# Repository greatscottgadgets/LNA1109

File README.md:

# LNA1109

LNA1109 is an in-line SMA Low Noise Amplifier with SAW filter.

## hardware notes

Schematic and layout files were designed in KiCad, an open source electronic
design automation package.

This design may be assembled with any SAW filter with a standard 1.1 x 0.9 mm
footprint.

The PCB is designed to fit the Crystek SMA-KIT-1.5MF housing.

```
order of copper layers:
    Copper 1:  F (front)
    Copper 2:  In1
    Copper 3:  In2
    Copper 4:  B (back)

PCB description: 4 layer PCB 0.8 mm
    Copper       1:  0.035 mm (1 oz)
    Dielectric 1-2:  0.2 mm prepreg
    Copper       2:  0.0175 mm (0.5 oz)
    Dielectric 2-3:  0.265 mm core
    Copper       3:  0.0175 mm (0.5 oz)
    Dielectric 3-4:  0.2 mm prepreg
    Copper       4:  0.035 mm (1 oz)

7628 prepreg with Er=4.6
double side solder mask green
double side silkscreen white
7 mil minimum trace width
5 mil minimum isolation
```

PCBs of this specification are available from JLCPCB (JLC7628 4-layer 0.8 mm stackup).

## frequency options

LNA1109 may be populated with different components to support various frequency
bands.

frequency band | U4 part number       | L1-L4 part number | C1-C6 part number
---------------|----------------------|-------------------|-------------------
902-928 MHz    | FAR-F5QA-915M00-M2AK | HK1005R10J-T      | GCM1555C1H470JA16D
1559-1606 MHz  | F6QA1G582H2JM        | HK100539NJ-T      | GCM1555C1H180JA16D
2402-2483 MHz  | F6FC2G441H4PE        | HK100527NJ-T      | GCM1555C1H100JA16D

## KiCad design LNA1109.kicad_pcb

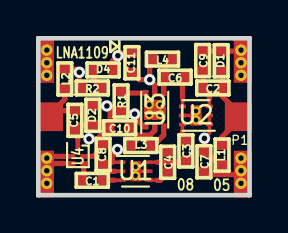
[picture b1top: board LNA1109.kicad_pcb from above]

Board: 4 copper layers, 11.7 x 8.7 mm, 25 parts (0 on the bottom side), 17 nets.

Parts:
C1, C2, C3, C4, C5, C6: 47pF; 0402
C7, C8: 100pF; 0402
C9: 1pF; 0402
C10, C11: 1uF; 0402
D1, D2: D_TVS; 0402
D4: LNALED; 0402
L1, L2, L3, L4: 100nH; 0402
P1: SMA-KIT-1.5MF
R1: 3k; 0402
R2: 470; 0402
U1, U2: SWITCH; GRF6011
U3: LNA; TSLP-7-1
U4: SAW; F5Q

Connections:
GND: C7.1, C8.1, C9.2, C10.1, C11.1, D1.1, D2.1, D4.1, P1.2, P1.4, U1.5, U1.7, U2.5, U2.7, U3.7, U4.2, U4.3, U4.5
unnamed: C1.1, U4.4
unnamed: C1.2, U1.3
unnamed: C2.1, C9.1, U2.3
unnamed: C2.2, D1.2, L1.1, P1.1
unnamed: C3.1, U1.6
unnamed: C3.2, U2.6
unnamed: C4.1, U1.4
unnamed: C4.2, L3.1, U3.3
unnamed: C5.1, L2.1, P1.3
unnamed: C5.2, D2.2, U4.1
unnamed: C6.1, L4.2, U3.4
unnamed: C6.2, U2.4
unnamed: C10.2, L3.2, U3.2
unnamed: D4.2, R2.2
unnamed: R1.2, U3.6
VCC: C7.2, C8.2, C11.2, L1.2, L2.2, L4.1, R1.1, R2.1, U1.1, U1.2, U2.1, U2.2, U3.1, U3.5

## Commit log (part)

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2020-08-05 initial commit, copied from LNA915 in hackrf repository
2020-08-05 update README markdown
2020-08-05 correct U4 track clearance
2020-08-05 renumber capacitor reference designators
2020-08-05 optimize part selection for 915 MHz
2020-08-05 document components for frequency band options
2020-08-05 rename from LNAF5Q to LNA1109
2020-08-05 adjust board name fit on silkscreen
2020-08-06 correct C7 and C8 part selection
2020-08-16 add missing fp-lib-table and sym-lib-table
2020-08-16 disable gerber advanced attributes

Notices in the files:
LNA1109.kicad_pcb:
Copyright (c) 2014-2020 Great Scott Gadgets
Licensed under the CERN-OHL-P v2
